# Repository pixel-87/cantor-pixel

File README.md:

# Cantor Keyboard Remix (36 keys)
This is a modified version of the [Cantor](https://github.com/diepala/cantor) keyboard, designed by [diepala](https://github.com/diepala).
This was later changed by [nilokr](https://github.com/nilokr) in the [Cantor-remix](https://github.com/nilokr/cantor-remix)

## Changes
I changed the silkscreen to one I liked better.

I followed the process documented on [this Ben Vallack's video](https://www.youtube.com/watch?v=JqpBKuEVinw) - it was quite simple. You can do the same if you want to change the silkscreen. 

## Firmware / Keymap
The 36 keys of this version are ideal for running [Miryoku](https://github.com/manna-harbour/miryoku), an ergonomic, minimal, orthogonal, and universal keyboard layout.

The original Cantor is already supported, so all you have to do is running the following command:
```
qmk flash -kb cantor -km manna-harbour_miryoku
```

Please note that as of 06/2022, an update for Miryoku is [pending review](https://github.com/qmk/qmk_firmware/pull/16482) - if you want to have the latest version you can merge the PR branch locally, or follow instructions discussed [here](https://github.com/manna-harbour/miryoku/discussions/89).

## Build Guide
Grab the `pcb/gerber.zip` and use your service of choice to order it! I used [JLCPCB](https://jlcpcb.com/), and there's a tag for them to print the order number in the silkscreen layer. 

Make sure to follow the original [Cantor Build Guide](https://github.com/diepala/cantor/blob/main/doc/build_guide.md). 

## Support Cantor
Consider supporting the original [Cantor](https://github.com/diepala/cantor)! Please refer to the original repository for more information.

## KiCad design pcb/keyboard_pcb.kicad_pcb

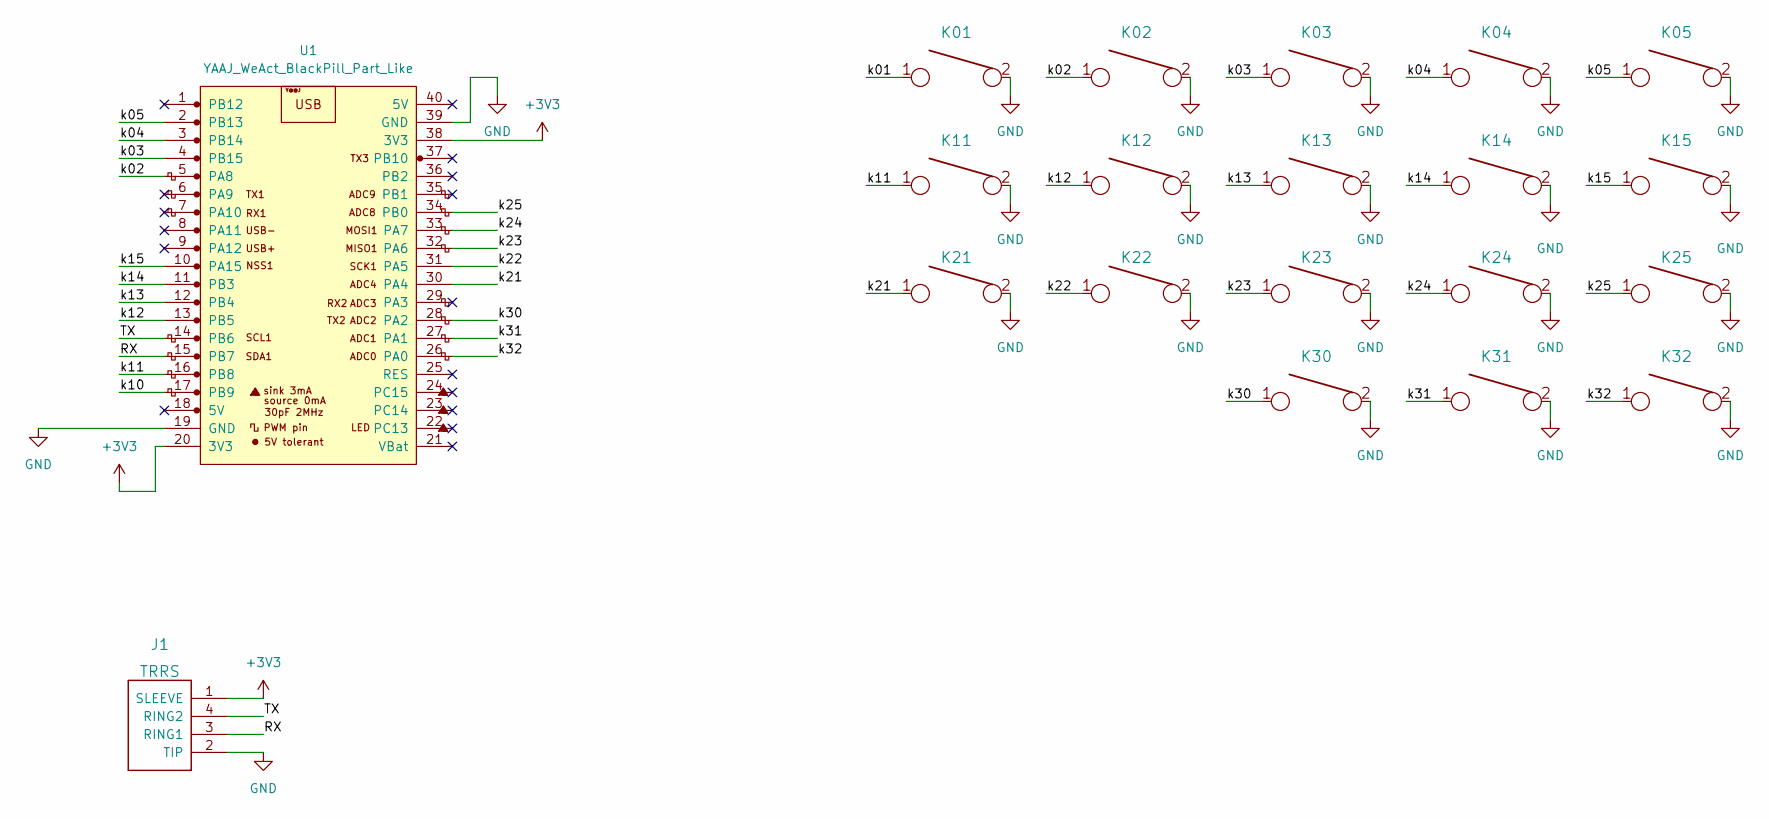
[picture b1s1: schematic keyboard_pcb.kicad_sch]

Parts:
J1: TRRS; TRRS-PJ-320A
K01, K02, K03, K04, K05, K11, K12, K13, K14, K15, K21, K22, K23, K24, K25, K30, K31, K32: KEYSW; SW_PG1350_reversible
U1: YAAJ_WeAct_BlackPill_Part_Like; YAAJ_WeAct_BlackPill_2

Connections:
+3V3: J1.1 (SLEEVE), U1.20 (3V3), U1.38 (3V3)
/RX: J1.3 (RING1), U1.15 (PB7)
/TX: J1.4 (RING2), U1.14 (PB6)
/k00: U1.35 (PB1)
/k01: K01.1, U1.37 (PB10)
/k02: K02.1, U1.5 (PA8)
/k03: K03.1, U1.4 (PB15)
/k04: K04.1, U1.3 (PB14)
/k05: K05.1, U1.2 (PB13)
/k10: U1.17 (PB9)
/k11: K11.1, U1.16 (PB8)
/k12: K12.1, U1.13 (PB5)
/k13: K13.1, U1.12 (PB4)
/k14: K14.1, U1.11 (PB3)
/k15: K15.1, U1.10 (PA15)
/k20: U1.29 (PA3)
/k21: K21.1, U1.30 (PA4)
/k22: K22.1, U1.31 (PA5)
/k23: K23.1, U1.32 (PA6)
/k24: K24.1, U1.33 (PA7)
/k25: K25.1, U1.34 (PB0)
/k30: K30.1, U1.28 (PA2)
/k31: K31.1, U1.27 (PA1)
/k32: K32.1, U1.26 (PA0)
GND: J1.2 (TIP), K01.2, K02.2, K03.2, K04.2, K05.2, K11.2, K12.2, K13.2, K14.2, K15.2, K21.2, K22.2, K23.2, K24.2, K25.2, K30.2, K31.2, K32.2, U1.19 (GND), U1.39 (GND)

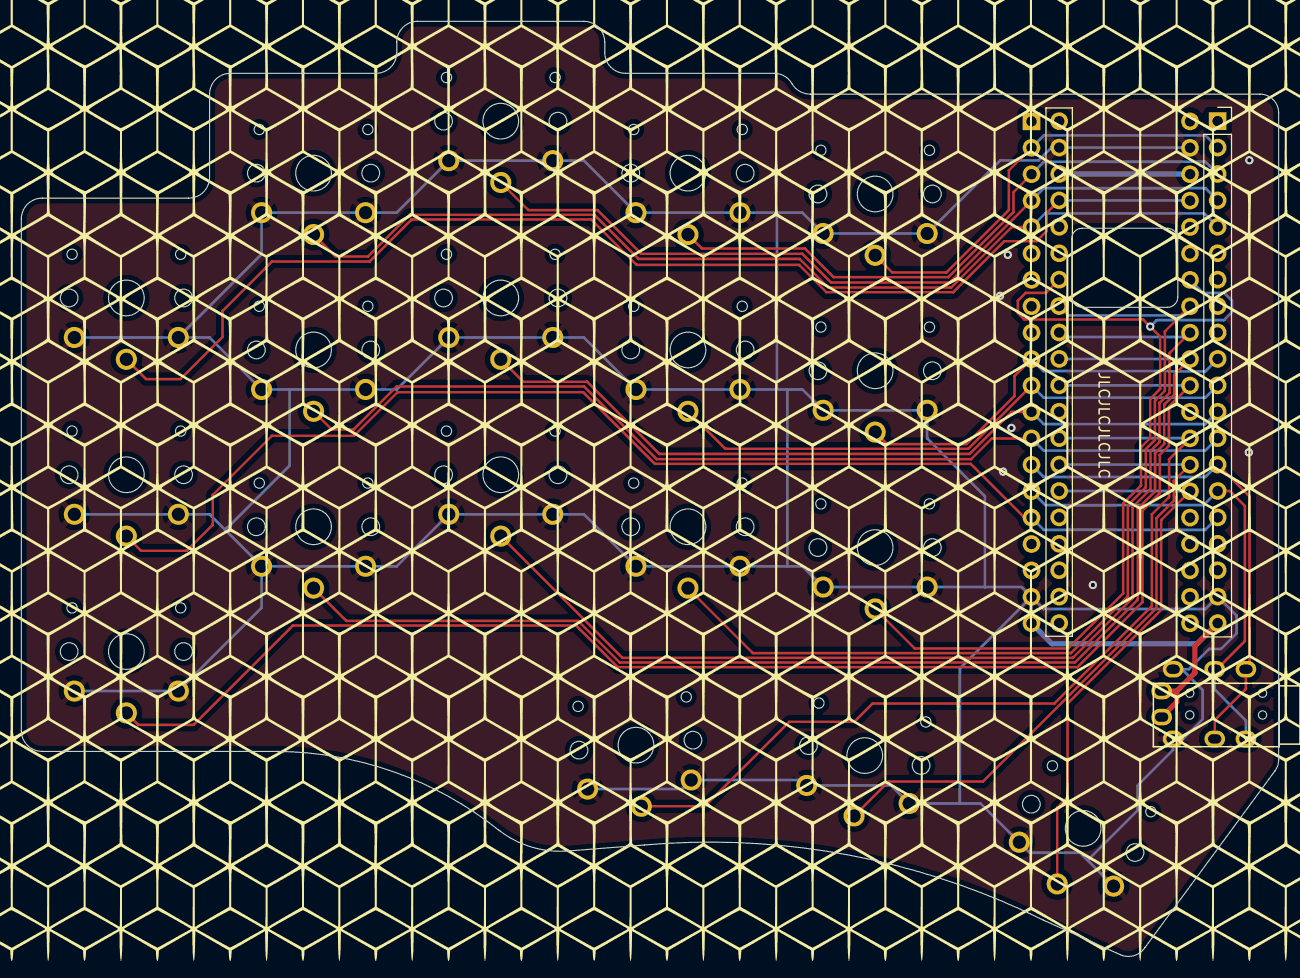
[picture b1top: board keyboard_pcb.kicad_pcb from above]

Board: 2 copper layers, 120.9 x 89.9 mm, 20 parts (0 on the bottom side), 22 nets.

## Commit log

2022-05-25 Mod to 36 keys and add silkscreen
2022-05-25 Generate gerber
2022-06-03 Change README
